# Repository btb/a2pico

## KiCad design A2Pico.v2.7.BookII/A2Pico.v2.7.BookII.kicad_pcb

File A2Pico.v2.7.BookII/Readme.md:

# A2Pico for Book II

A2Pico Version 2.7.BookII is derived from the A2Pico version 2.7, made to fit in the internal slot 7 of the [Book II](https://8086cpu.com/Z80/6502/110.html) from 8086cpu.com. It omits the slide switch and power LED from v2.7.

## Todo

* Replace USB micro-B connector with type C.

* Fabricate a new rear panel with openings for the micro SD card and USB port.

## RPI Usage

| GPIO    | Usage     |
|:--------|:----------|
| 0       |  UART Tx  |
| 1       |  UART Rx  |
| 2       |  ENBL     |
| 3 - 10  | AD0 - AD7 |
| 11 - 14 | A8 - A11  |
| 15      | R/W       |
| 16      | Ф1        |
| 17      | RES       |
| 18      | IRQ       |
| 19      | CMD       |
| 20      | DAT0      |
| 21      | DAT3      |
| 22      | CLK       |
| 26      | AL-OE     |
| 27      | D-OE      |
| 28      | DDIR      |

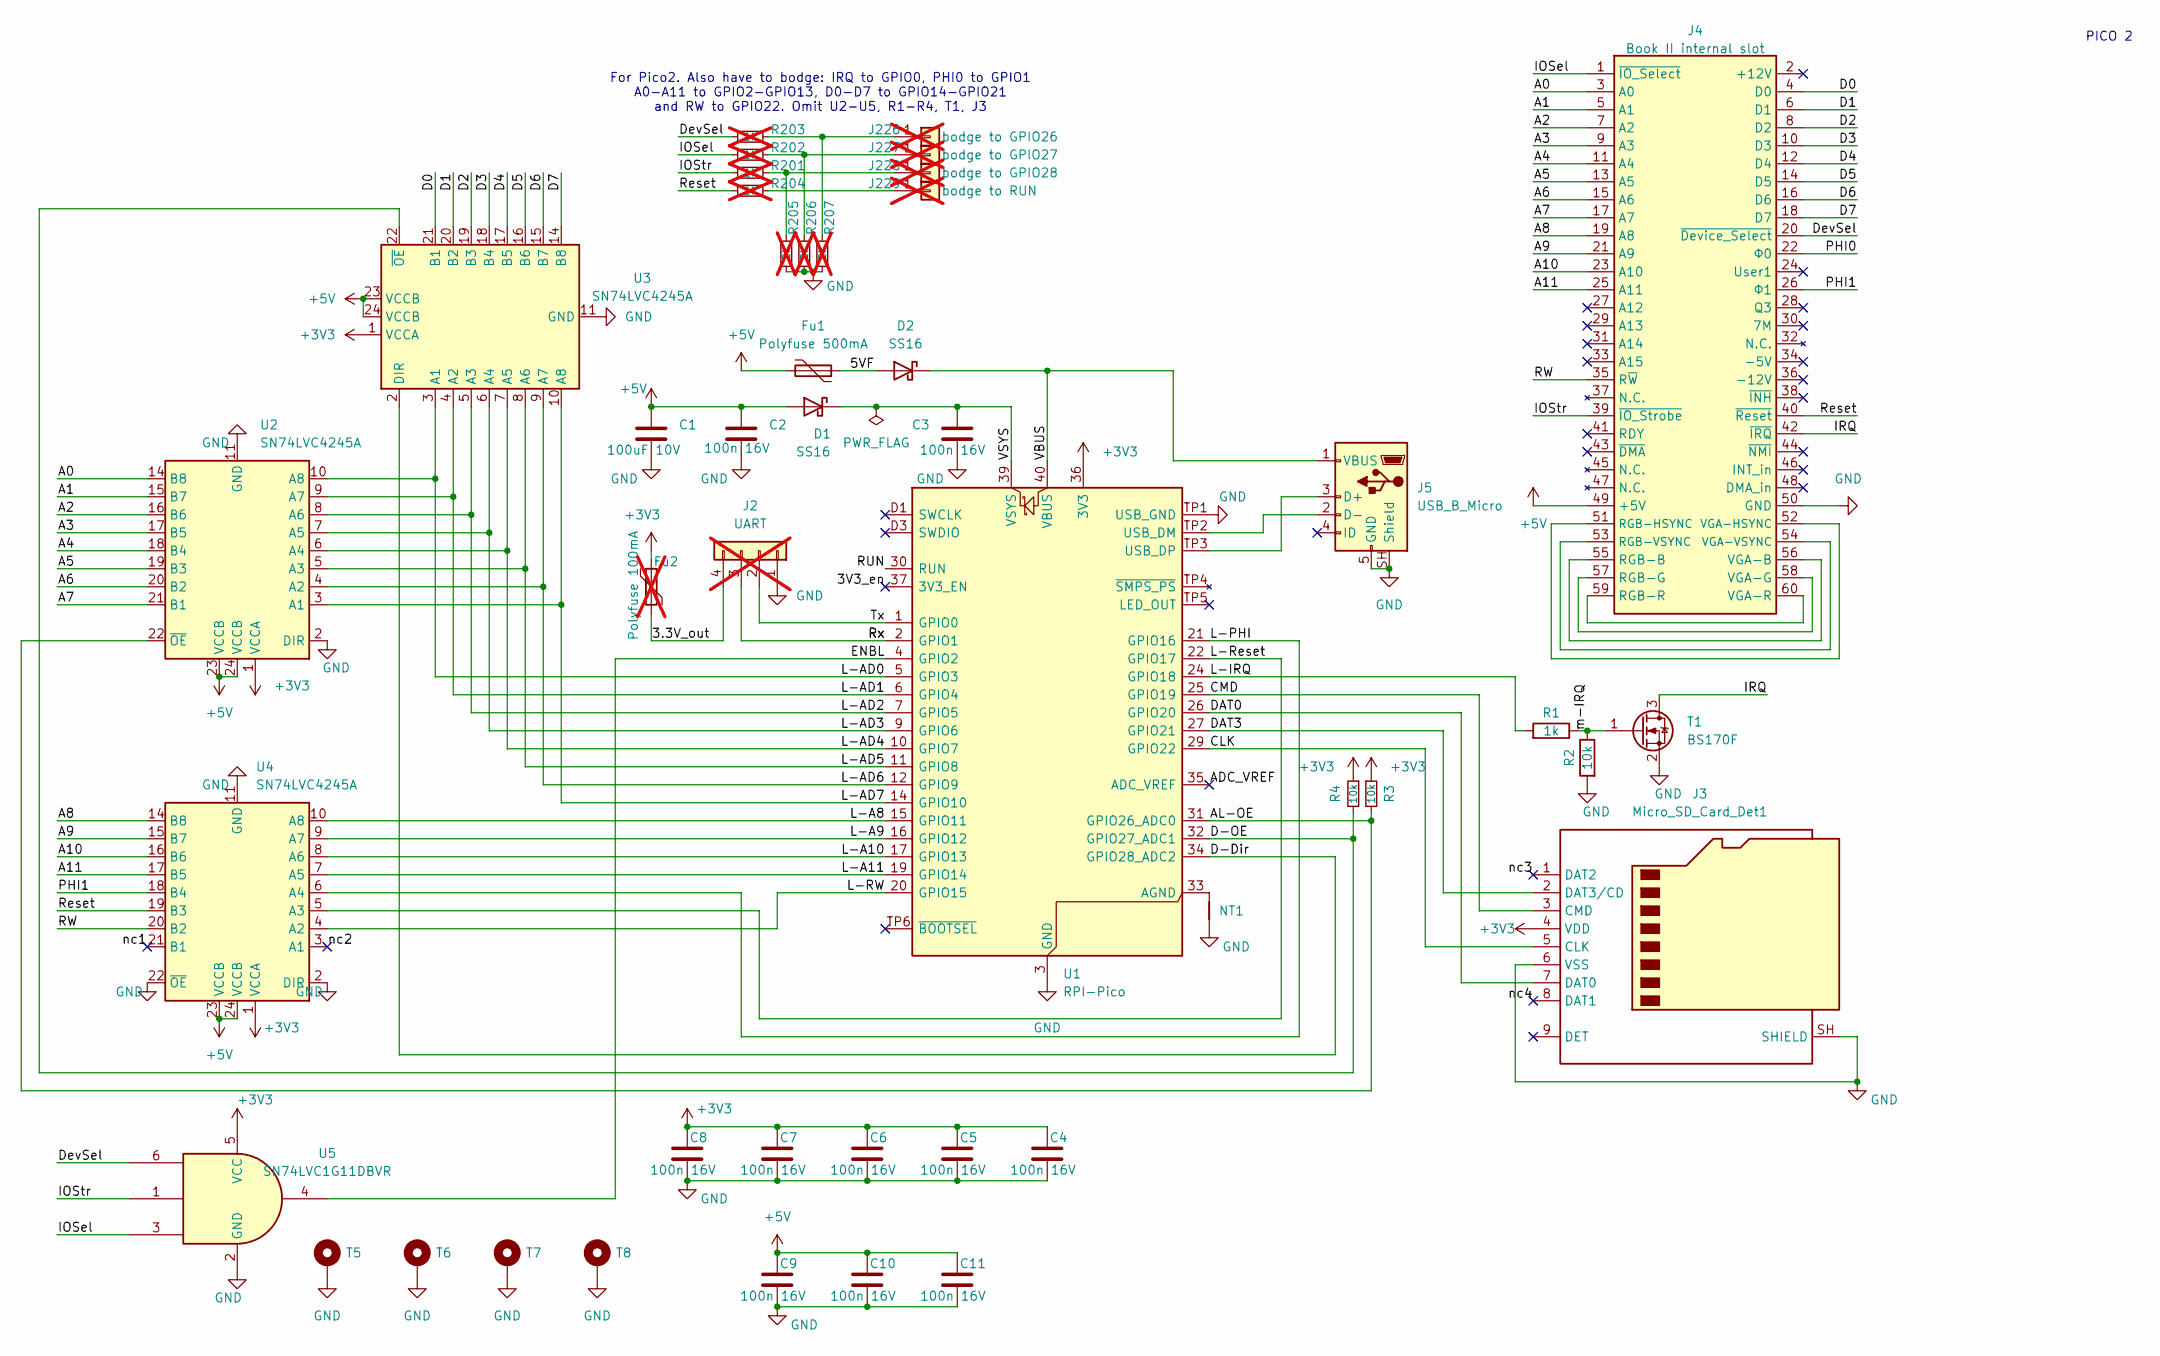
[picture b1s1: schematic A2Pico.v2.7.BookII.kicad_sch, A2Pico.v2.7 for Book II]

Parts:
C1: 100uF 10V; C_1206_3216Metric_Pad1.33x1.80mm_HandSolder; JLCPCB Part # C15008
C2, C3, C4, C5, C6, C7, C8, C9, C10, C11: 100n 16V; C_0603_1608Metric_Pad1.08x0.95mm_HandSolder; JLCPCB Part # C14663
D1, D2: SS16; D_SMA_Handsoldering; JLCPCB Part # C2480
Fu1: Polyfuse 500mA; Fuse_0805_2012Metric_Pad1.15x1.40mm_HandSolder; JLCPCB Part # C269102
Fu2: Polyfuse 100mA; Fuse_0805_2012Metric_Pad1.15x1.40mm_HandSolder; JLCPCB Part # C269101; not fitted
J2: UART; PinHeader_1x04_P2.54mm_Horizontal; not fitted
J3: Micro_SD_Card_Det1; MicroSD_CUI_MSD-4-A; JLCPCB Part # C52750848
J4: Book II internal slot; PinSocket_2x30_P2.54mm_Vertical
J5: USB_B_Micro; USB_Micro-B_Amphenol_10118193-0001LF_Horizontal; JLCPCB Part # C6798311
J226: bodge to GPIO26; PinHeader_1x01_P1.00mm_Vertical; not fitted
J227: bodge to GPIO27; PinHeader_1x01_P1.00mm_Vertical; not fitted
J228: bodge to GPIO28; PinHeader_1x01_P1.00mm_Vertical; not fitted
J229: bodge to RUN; PinHeader_1x01_P1.00mm_Vertical; not fitted
NT1: (no value)
R1: 1k; R_0603_1608Metric_Pad0.98x0.95mm_HandSolder; JLCPCB Part # C21190
R2, R3, R4: 10k; R_0603_1608Metric_Pad0.98x0.95mm_HandSolder; JLCPCB Part # C25804
R201, R202, R203, R204: 1k; R_0603_1608Metric_Pad0.98x0.95mm_HandSolder; not fitted
R205, R206, R207: 2k; R_0603_1608Metric_Pad0.98x0.95mm_HandSolder; not fitted
T1: BS170F; SOT-23_Handsoldering; JLCPCB Part # C8545
T5, T6, T7, T8: MountingHole_Pad; M2.8D4.5
U1: RPI-Pico
U2, U3, U4: SN74LVC4245A; TSSOP-24_4.4x7.8mm_P0.65mm; JLCPCB Part # C7859
U5: SN74LVC1G11DBVR; SOT-23-6_Handsoldering; JLCPCB Part # C22046

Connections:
+3V3: C4.1, C5.1, C6.1, C7.1, C8.2, Fu2.1, J3.4 (VDD), R3.1, R4.1, U1.36 (3V3), U2.1 (VCCA), U3.1 (VCCA), U4.1 (VCCA), U5.5 (VCC)
+5V: C1.1, C2.1, C9.2, C10.1, C11.1, D1.2 (A), Fu1.2, J4.49 (+5V), U2.23 (VCCB), U2.24 (VCCB), U3.23 (VCCB), U3.24 (VCCB), U4.23 (VCCB), U4.24 (VCCB)
/3.3V_out: Fu2.2, J2.4
/3V3_en: U1.37 (3V3_EN)
/5VF: D2.2 (A), Fu1.1
/A0: J4.3 (A0), U2.14 (B8)
/A1: J4.5 (A1), U2.15 (B7)
/A2: J4.7 (A2), U2.16 (B6)
/A3: J4.9 (A3), U2.17 (B5)
/A4: J4.11 (A4), U2.18 (B4)
/A5: J4.13 (A5), U2.19 (B3)
/A6: J4.15 (A6), U2.20 (B2)
/A7: J4.17 (A7), U2.21 (B1)
/A8: J4.19 (A8), U4.14 (B8)
/A9: J4.21 (A9), U4.15 (B7)
/A10: J4.23 (A10), U4.16 (B6)
/A11: J4.25 (A11), U4.17 (B5)
/ADC_VREF: U1.35 (ADC_VREF)
/AL-OE: R3.2, U1.31 (GPIO26_ADC0), U2.22 (~OE)
/CLK: J3.5 (CLK), U1.29 (GPIO22)
/CMD: J3.3 (CMD), U1.25 (GPIO19)
/D0: J4.4 (D0), U3.21 (B1)
/D1: J4.6 (D1), U3.20 (B2)
/D2: J4.8 (D2), U3.19 (B3)
/D3: J4.10 (D3), U3.18 (B4)
/D4: J4.12 (D4), U3.17 (B5)
/D5: J4.14 (D5), U3.16 (B6)
/D6: J4.16 (D6), U3.15 (B7)
/D7: J4.18 (D7), U3.14 (B8)
/D-Dir: U1.34 (GPIO28_ADC2), U3.2 (DIR)
/D-OE: R4.2, U1.32 (GPIO27_ADC1), U3.22 (~OE)
/DAT0: J3.7 (DAT0), U1.26 (GPIO20)
/DAT3: J3.2 (DAT3/CD), U1.27 (GPIO21)
/DevSel: J4.20 (~Device_Select), R203.1, U5.6
/ENBL: U1.4 (GPIO2), U5.4
/IOSel: J4.1 (~IO_Select), R202.1, U5.3
/IOStr: J4.39 (~IO_Strobe), R201.1, U5.1
/IRQ: J4.42 (~IRQ), T1.3 (D)
/L-A8: U1.15 (GPIO11), U4.10 (A8)
/L-A9: U1.16 (GPIO12), U4.9 (A7)
/L-A10: U1.17 (GPIO13), U4.8 (A6)
/L-A11: U1.19 (GPIO14), U4.7 (A5)
/L-AD0: U1.5 (GPIO3), U2.10 (A8), U3.3 (A1)
/L-AD1: U1.6 (GPIO4), U2.9 (A7), U3.4 (A2)
/L-AD2: U1.7 (GPIO5), U2.8 (A6), U3.5 (A3)
/L-AD3: U1.9 (GPIO6), U2.7 (A5), U3.6 (A4)
/L-AD4: U1.10 (GPIO7), U2.6 (A4), U3.7 (A5)
/L-AD5: U1.11 (GPIO8), U2.5 (A3), U3.8 (A6)
/L-AD6: U1.12 (GPIO9), U2.4 (A2), U3.9 (A7)
/L-AD7: U1.14 (GPIO10), U2.3 (A1), U3.10 (A8)
/L-IRQ: R1.2, U1.24 (GPIO18)
/L-PHI: U1.21 (GPIO16), U4.6 (A4)
/L-RW: U1.20 (GPIO15), U4.4 (A2)
/L-Reset: U1.22 (GPIO17), U4.5 (A3)
/PHI0: J4.22 (Ф0)
/PHI1: J4.26 (Ф1), U4.18 (B4)
/RUN: U1.30 (RUN)
/RW: J4.35 (R~W), U4.20 (B2)
/Reset: J4.40 (~Reset), R204.1, U4.19 (B3)
/Rx: J2.3, U1.2 (GPIO1)
/Tx: J2.2, U1.1 (GPIO0)
/VBUS: D2.1 (K), J5.1 (VBUS), U1.40 (VBUS)
/VSYS: C3.1, D1.1 (K), U1.39 (VSYS)
/m-IRQ: R1.1, R2.1, T1.1 (G)
/nc1: U4.21 (B1)
/nc2: U4.3 (A1)
/nc3: J3.1 (DAT2)
/nc4: J3.8 (DAT1)
GND: C1.2, C2.2, C3.2, C4.2, C5.2, C6.2, C7.2, C8.1, C9.1, C10.2, C11.2, J2.1, J3.6 (VSS), J3.SH (SHIELD), J4.50 (GND), J5.5 (GND), J5.SH (Shield), NT1.2, R2.2, R205.1, R206.1, R207.1, T1.2 (S), T5.1 (1_1), T6.1 (1_1), T7.1 (1_1), T8.1 (1_1), U1.3 (GND), U1.8 (GND), U1.13 (GND), U1.18 (GND), U1.23 (GND), U1.28 (GND), U1.38 (GND), U1.D2 (GND), U1.TP1 (USB_GND), U2.2 (DIR), U2.11 (GND), U2.12 (GND), U2.13 (GND), U3.11 (GND), U3.12 (GND), U3.13 (GND), U4.2 (DIR), U4.11 (GND), U4.12 (GND), U4.13 (GND), U4.22 (~OE), U5.2 (GND)
unnamed: J4.55 (RGB-B), J4.56 (VGA-B)
unnamed: J4.57 (RGB-G), J4.58 (VGA-G)
unnamed: J4.51 (RGB-HSYNC), J4.52 (VGA-HSYNC)
unnamed: J4.59 (RGB-R), J4.60 (VGA-R)
unnamed: J4.53 (RGB-VSYNC), J4.54 (VGA-VSYNC)
unnamed: J5.3 (D+), U1.TP3 (USB_DP)
unnamed: J5.2 (D-), U1.TP2 (USB_DM)
unnamed: J226.1 (Pin_1_1), R203.2, R207.2
unnamed: J227.1 (Pin_1_1), R202.2, R206.2
unnamed: J228.1 (Pin_1_1), R201.2, R205.2
unnamed: J229.1 (Pin_1_1), R204.2
unnamed: NT1.1, U1.33 (AGND)

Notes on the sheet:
PICO 2
For Pico2. Also have to bodge: IRQ to GPIO0, PHI0 to GPIO1 A0-A11 to GPIO2-GPIO13, D0-D7 to GPIO14-GPIO21 and RW to GPIO22. Omit U2-U5, R1-R4, T1, J3

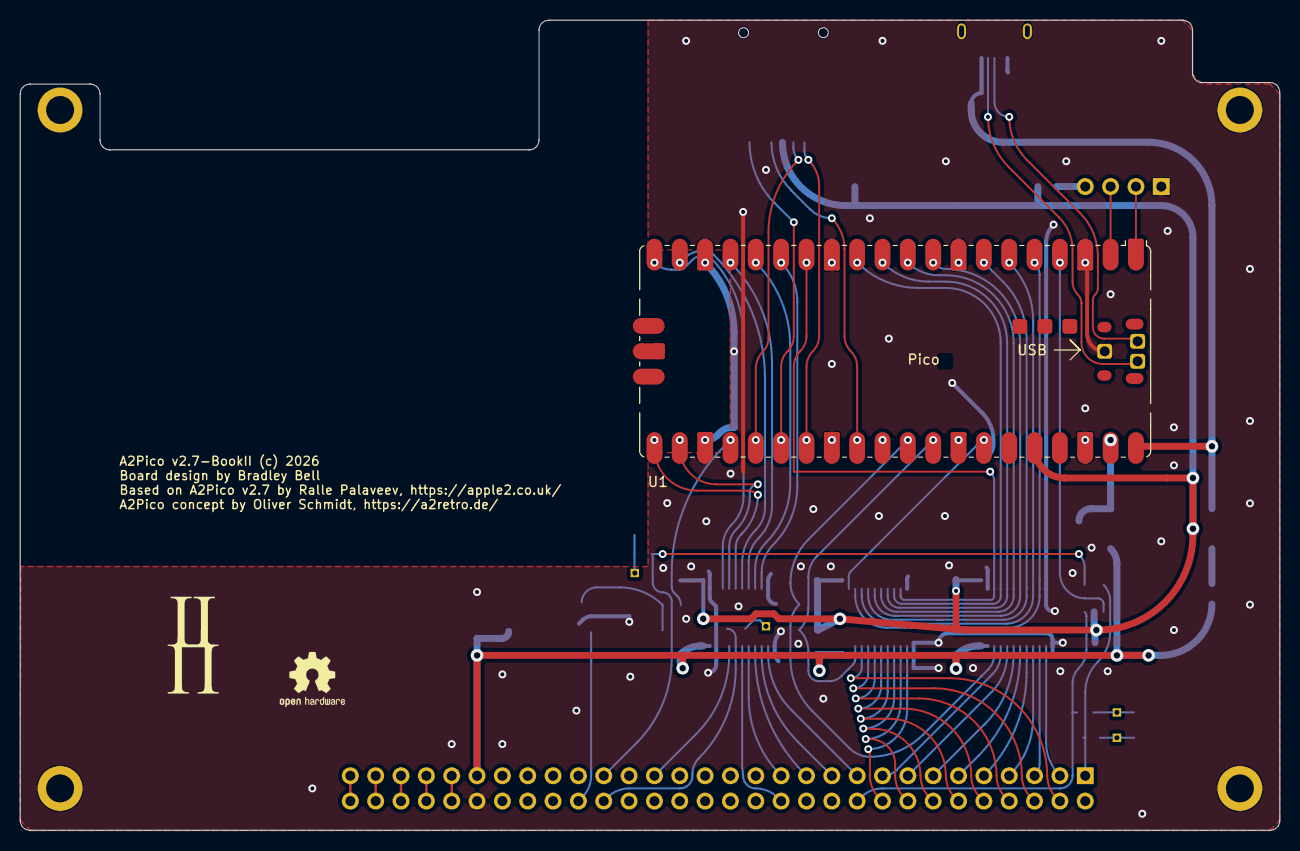
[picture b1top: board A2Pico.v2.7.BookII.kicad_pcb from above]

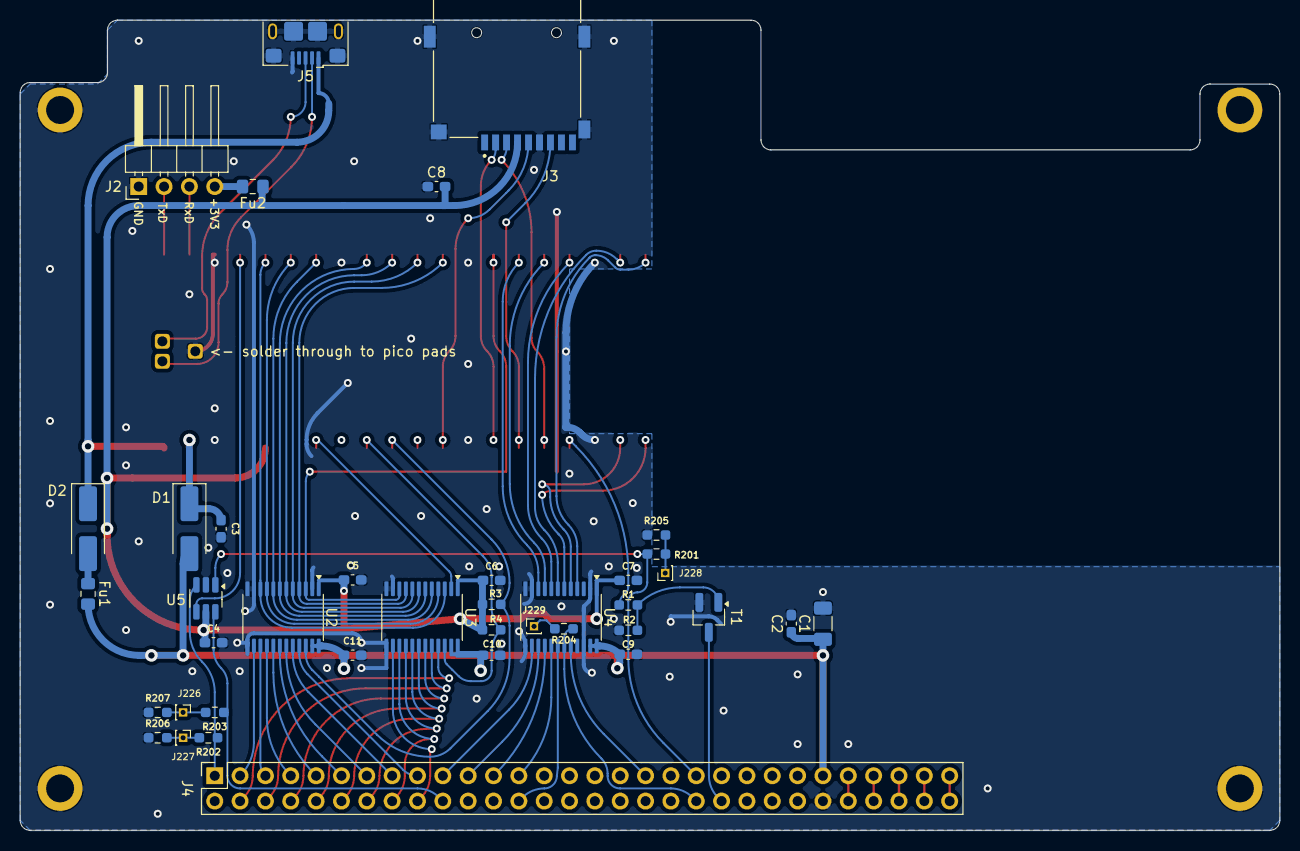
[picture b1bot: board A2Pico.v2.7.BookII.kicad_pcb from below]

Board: 2 copper layers, 126.2 x 81.2 mm, 44 parts (39 on the bottom side), 72 nets.

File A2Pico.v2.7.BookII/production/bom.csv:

Designator,Footprint,Quantity,Value,LCSC Part #
C1,1206,1,100uF 10V,C15008
"C10, C11, C2, C3, C4, C5, C6, C7, C8, C9",0603,10,100n 16V,C14663
"D1, D2",D_SMA_Handsoldering,2,SS16,C2480
FU1,0805,1,Polyfuse 500mA,C269102
J3,MicroSD_CUI_MSD-4-A,1,Micro_SD_Card_Det1,C52750848
J5,USB_Micro-B_Amphenol_10118193-0001LF_Horizontal,1,USB_B_Micro,C6798311
R1,0603,1,1k,C21190
"R2, R3, R4",0603,3,10k,C25804
T1,SOT-23_Handsoldering,1,BS170F,C8545
U1,RaspberryPi_Pico_SMD,1,RPI-Pico,
"U2, U3, U4",TSSOP-24_4.4x7.8mm_P0.65mm,3,SN74LVC4245A,C7859
U5,SOT-23-6_Handsoldering,1,SN74LVC1G11DBVR,C22046

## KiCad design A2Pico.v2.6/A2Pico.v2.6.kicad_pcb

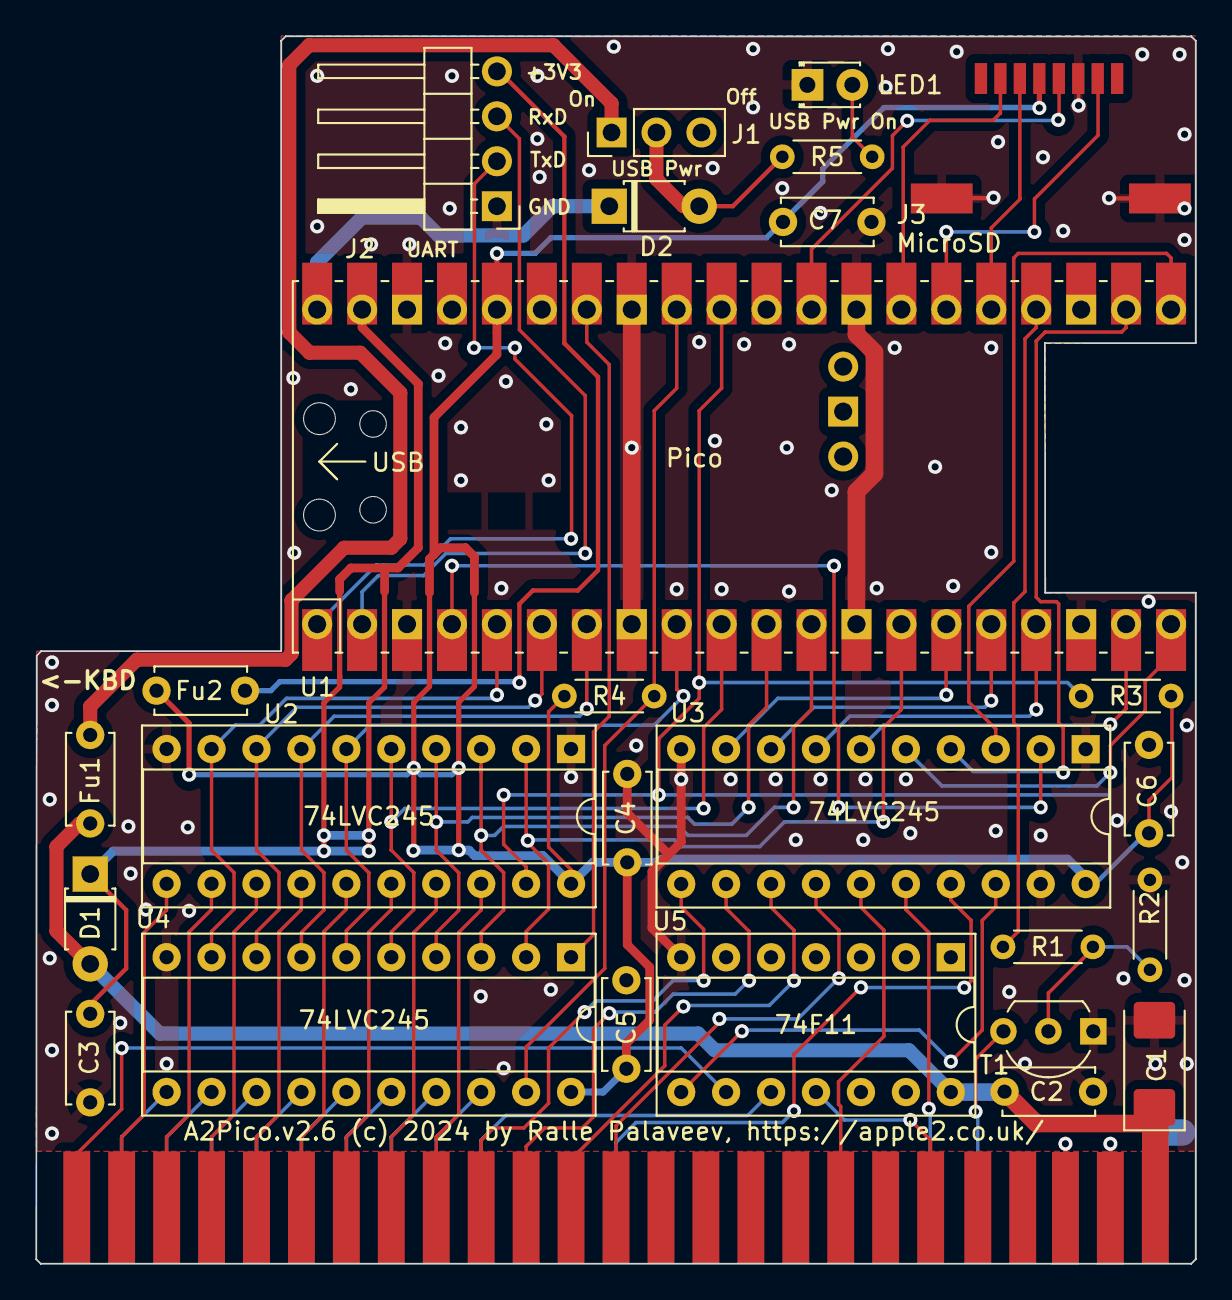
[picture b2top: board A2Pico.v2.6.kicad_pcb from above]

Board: 2 copper layers, 65.5 x 69.4 mm, 25 parts (0 on the bottom side), 31 nets.

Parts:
C1: 220uF; CP_EIA-6032-15_Kemet-U
C2, C3, C4, C5, C6, C7: 100n; C_Disc_D5.0mm_W2.5mm_P5.00mm
D1, D2: D_T-1_P5.08mm_Horizontal
Fu1: 500mA; C_Disc_D5.0mm_W2.5mm_P5.00mm
Fu2: 100mA; C_Disc_D5.0mm_W2.5mm_P5.00mm
J1: PinHeader_1x03_P2.54mm_Vertical
J2: PinHeader_1x04_P2.54mm_Horizontal
LED1: LED_D1.8mm_W3.3mm_H2.4mm
R1, R5: 1k; R_Axial_DIN0204_L3.6mm_D1.6mm_P5.08mm_Horizontal
R2, R3, R4: 10k; R_Axial_DIN0204_L3.6mm_D1.6mm_P5.08mm_Horizontal
T1: TO-92L_Inline_Wide
U1: Pico / PicoW; RPi_PicoW_SMD_TH
U2, U3, U4: 74LVC245; DIP-20_W7.62mm_Socket
U5: 74F11; DIP-14_W7.62mm_Socket

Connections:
3.3V: C4.1, C5.1, C6.1, C7.1, Fu2.1, R3.1, R4.2, U1.36 (3V3), U2.20, U3.20, U4.20
3.3V_out: Fu2.2, J2.4
5V: C1.1, C2.2, D1.2, Fu1.1, U5.14
AL-OE: R3.2, U1.31 (GPIO26_ADC0), U2.19
D-Dir: U1.34 (GPIO28_ADC2), U4.1
D-OE: R4.1, U1.32 (GPIO27_ADC1), U4.19
ENBL: U3.18, U5.8
GND: C1.2, C2.1, C3.1, C4.2, C5.2, C6.2, C7.2, J2.1, LED1.1, R2.2, T1.1, U1.3 (GND), U1.8 (GND), U1.13 (GND), U1.18 (GND), U1.23 (GND), U1.28 (GND), U1.33 (AGND), U1.38 (GND), U2.1, U2.10, U3.1, U3.10, U3.19, U4.10, U5.7
J1-1: Fu1.2, J1.1
J1-2: D2.2, J1.2, R5.2
L-A8: U1.15 (GPIO11), U3.9
L-A9: U1.16 (GPIO12), U3.8
L-A10: U1.17 (GPIO13), U3.7
L-A11: U1.19 (GPIO14), U3.6
L-AD0: U1.5 (GPIO3), U2.9, U4.9
L-AD1: U1.6 (GPIO4), U2.8, U4.8
L-AD2: U1.7 (GPIO5), U2.7, U4.7
L-AD3: U1.9 (GPIO6), U2.6, U4.6
L-AD4: U1.10 (GPIO7), U2.5, U4.5
L-AD5: U1.11 (GPIO8), U2.4, U4.4
L-AD6: U1.12 (GPIO9), U2.3, U4.3
L-AD7: U1.14 (GPIO10), U2.2, U4.2
L-ENBL: U1.4 (GPIO2), U3.2
L-IRQ: R1.2, U1.24 (GPIO18)
L-PHI1: U1.21 (GPIO16), U3.3
L-RW: U1.20 (GPIO15), U3.5
L-Reset: U1.22 (GPIO17), U3.4
Rx: J2.3, U1.2 (GPIO1)
Tx: J2.2, U1.1 (GPIO0)
VBUS: D2.1, U1.40 (VBUS)
VSYS: C3.2, D1.1, U1.39 (VSYS)

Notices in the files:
A2Pico.v2.6/A2Pico.v2.6.kicad_pcb:
A2Pico v2.6 (c) 2024
A2Pico.v2.6 (c) 2024 by Ralle Palaveev, https://apple2.co.uk
A2Pico.v2.7.BookII/A2Pico.v2.7.BookII.kicad_pcb:
A2Pico v2.7-BookII (c) 2026
